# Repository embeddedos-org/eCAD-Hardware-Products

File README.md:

# eCAD Hardware Products

Hardware / PCB CAD design collection for the **EmbeddedOS (EoS)** ecosystem.
The repository organizes hardware product designs by application domain. Each
domain holds one or more product lines, and each product line typically carries
a product datasheet, a bill of materials (`bom.csv`), power-budget simulation
scripts, and placeholder directories for PCB and mechanical CAD artifacts.
Several product lines also include KiCad schematics (`*.kicad_sch`).

> Status varies by design. Directories are at different maturity levels (many
> "Design" / "Pre-production"); PCB and CAD folders often contain `.gitkeep`
> placeholders rather than finished layouts. Check each design's own `README.md`
> and `docs/` for its current state.

## Domains

The repository contains **16** domain design collections:

| Domain | Focus |
|---|---|
| `eAerospace_CAD_Design` | Aircraft components, avionics, UAV/drone systems, space systems |
| `eConsumer_CAD_Design` | Smart home devices, personal wearables, AR/smart devices |
| `eCybersecurity_CAD_Design` | Security appliances and physical security systems |
| `eDefense_CAD_Design` | Surveillance, tactical communications, protection equipment |
| `eElectronics_CAD_Design` | PCBs, embedded controllers, RF modules, FPGAs, AI accelerators |
| `eEnergy_CAD_Design` | Battery products, renewable energy systems, power electronics |
| `eHealth365_CAD_Design` | Two-device health monitoring system (smart patch / smart ring) |
| `eIndustrial_CAD_Design` | Sensors, industrial electronics, infrastructure equipment |
| `eMedical_CAD_Design` | Diagnostic, surgical, patient-care, laboratory equipment |
| `eMining_CAD_Design` | Autonomous mining/construction equipment, industrial safety systems |
| `ePAM_CAD_Design` | Personal air/ground mobility — solar-hybrid transport, 4-product line |
| `eRadar360_CAD_Design` | 360° automotive safety radar + laser + V2X + AI threat detection |
| `eRobotics_CAD_Design` | Industrial robots, autonomous systems, robot components |
| `eSmartCity_CAD_Design` | Urban infrastructure, utilities, telecommunications |
| `eTransport_CAD_Design` | Automotive electronics, rail systems, maritime systems |
| `eosHealth_CAD_Design` | Four-device wearable health platform |

Plus:

- `future_designs/` — early/prospective concepts (e.g. `eBCI-Lite`)
- `docs/` — repository-level documentation

## Typical design layout

Most domains follow a common structure, for example:

```
eAerospace_CAD_Design/
  README.md
  docs/                      business_plan.md, regulatory_path.md
  ebuild_simulation/         eBuild simulation notes
  <product_line>/
    product_datasheet.md
    bom.csv
    simulation/power_budget_sim.py
    hardware/
      pcb/  cad/  antenna/   (artifact folders; often .gitkeep placeholders)
```

Artifact formats present in the repo include Markdown datasheets, CSV BOMs,
Python simulation scripts, and KiCad schematics (`*.kicad_sch`). Some product
lines also include TypeScript/Dart companion app sources and 3D-model notes.

## Simulations

Power-budget simulations are plain Python scripts, runnable per product line:

```bash
cd eAerospace_CAD_Design/<product_line>/simulation/
python3 power_budget_sim.py
```

Design docs reference the [EoSim](https://github.com/embeddedos-org/EoSim)
digital-twin platform for hardware-in-the-loop testing. Running one script alone
does not establish that a product is validated.

## Evidence-backed product validation

The committed `tools/catalog/product_inventory.json` is the complete product
execution set. The v1 contract schemas and policy requirements are documented in
`docs/hardware-validation-contract-v1.md`.

Discover inventory drift and inspect local tool capabilities:

```bash
python3 tools/validate_products.py discover
python3 tools/validate_products.py capabilities
```

Execute V0-V4 for every inventoried product and write hash-bound receipts:

```bash
python3 tools/validate_products.py validate \
  --all \
  --output /tmp/ecad-validation \
  --mode evidence
python3 tools/validate_products.py verify-bundle \
  /tmp/ecad-validation/bundle.json
```

`--mode evidence` succeeds when the selected inventory was executed and valid
receipts were written. Individual products may still be honestly `FAIL`,
`BLOCKED`, `INCONCLUSIVE`, or `NOT_RUN`. Use `--mode gate` for a release check;
it succeeds only when every selected product has real `PASS` evidence for V0,
V1, V2, V3, and V4. Historical baseline entries never waive a failed or missing
requirement.

## License

MIT — see [LICENSE](LICENSE).

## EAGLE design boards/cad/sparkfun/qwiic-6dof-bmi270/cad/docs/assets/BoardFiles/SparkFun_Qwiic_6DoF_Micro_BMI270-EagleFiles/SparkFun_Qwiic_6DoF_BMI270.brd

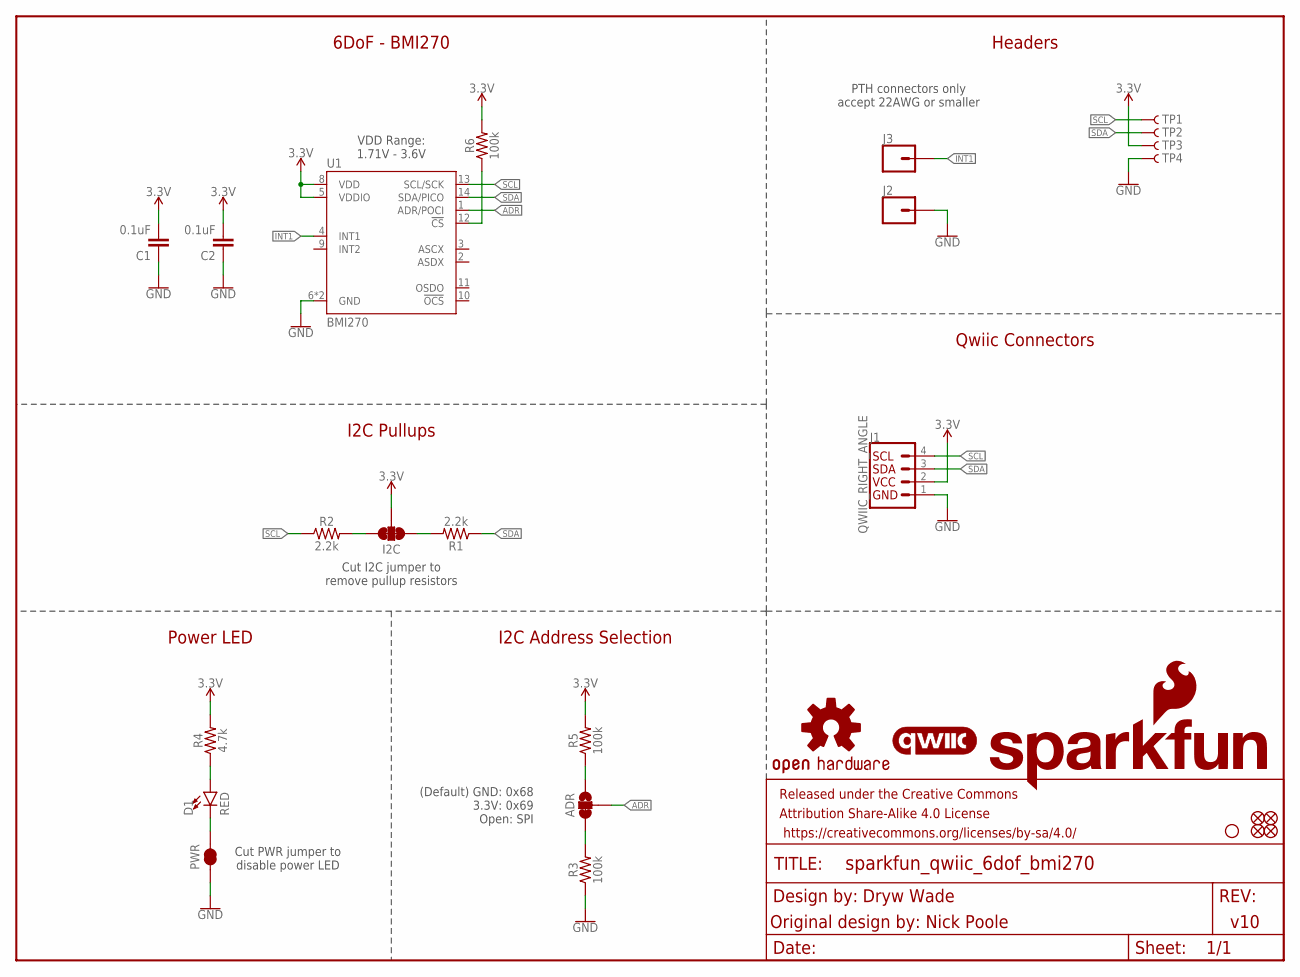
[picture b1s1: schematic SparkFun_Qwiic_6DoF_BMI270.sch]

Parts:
ADR: JUMPER-SMT_3_1-NC_TRACE_SILK; SMT-JUMPER_3_1-NC_TRACE_SILK
C1, C2: 0.1uF; 0402-TIGHT
D1: RED; LED-0402
FD1, FD2, FD3, FD4: FIDUCIALUFIDUCIAL; FIDUCIAL-MICRO
FRAME1: FRAME-LETTER; CREATIVE_COMMONS
H1: STAND-OFF
I2C: JUMPER-SMT_3_2-NC_TRACE_SILK; SMT-JUMPER_3_2-NC_TRACE_SILK
J1: QWIIC_RIGHT_ANGLE; JST04_1MM_RA
J2, J3: CONN_01_1MM; 1X01_1MM_NO_SILK
LOGO1: SFE_LOGO_NAME_FLAMEBLANK; BLANK
LOGO2: QWIIC_LOGO_3MM; QWIIC_3MM
LOGO3: OSHW-LOGOMINI; OSHW-LOGO-MINI
PWR: JUMPER-SMT_2_NC_TRACE_SILK; SMT-JUMPER_2_NC_TRACE_SILK
R1, R2: 2.2k; 0402-TIGHT
R3, R5, R6: 100k; 0402-TIGHT
R4: 4.7k; 0402-TIGHT
TP1, TP2, TP3, TP4: TEST-POINT3; PAD.03X.03
U1: BMI270

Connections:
3.3V: C1.2, C2.2, I2C.2, J1.2, R4.2, R5.2, R6.2, TP3.1, U1.5 (VDDIO), U1.8 (VDD)
ADR: ADR.2, U1.1 (ADR/POCI)
GND: C1.1, C2.1, J1.1, J2.1, PWR.1, R3.1, TP4.1, U1.6 (GND), U1.7 (GND)
INT1: J3.1, U1.4 (INT1)
unnamed: I2C.1, R1.2
unnamed: I2C.3, R2.2
unnamed: D1.C, PWR.2
unnamed: D1.A, R4.1
unnamed: ADR.1, R5.1
unnamed: ADR.3, R3.2
unnamed: R6.1, U1.12 (!CS!)
SCL: J1.4, R2.1, TP1.1, U1.13 (SCL/SCK)
SDA: J1.3, R1.1, TP2.1, U1.14 (SDA/PICO)

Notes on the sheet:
(Default) GND: 0x68 3.3V: 0x69 Open: SPI
Cut PWR jumper to disable power LED
Power LED
Headers
Qwiic Connectors
Dryw Wade
Original design by: Nick Poole
v10
6DoF - BMI270
Cut I2C jumper to remove pullup resistors
VDD Range: 1.71V - 3.6V
I2C Address Selection
I2C Pullups
PTH connectors only accept 22AWG or smaller

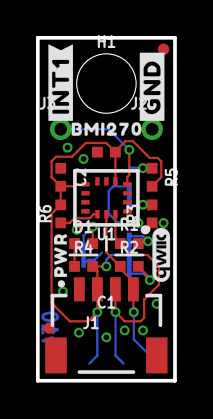
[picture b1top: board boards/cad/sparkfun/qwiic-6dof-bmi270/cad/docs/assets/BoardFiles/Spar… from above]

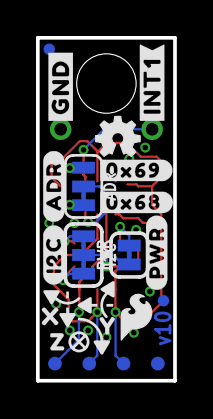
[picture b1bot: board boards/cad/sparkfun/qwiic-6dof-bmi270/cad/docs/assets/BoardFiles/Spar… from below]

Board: 2 copper layers, 7.6 x 19.1 mm, 45 parts (22 on the bottom side), 13 nets.

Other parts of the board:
U$1: #I2C#0
U$2, U$7: #GND#0
U$3: SFE_LOGO_FLAME_.1
U$4: #PWR#0
U$5: #ADR#0
U$6: #0X68#0
U$8, U$9: #INT1#0
U$18: #0X69#0
U$21: BMI2700
U$33: ORDERING_INSTRUCTIONS
U$34: PWR0
U$79: X0
U$80: Y0
U$81: Z0

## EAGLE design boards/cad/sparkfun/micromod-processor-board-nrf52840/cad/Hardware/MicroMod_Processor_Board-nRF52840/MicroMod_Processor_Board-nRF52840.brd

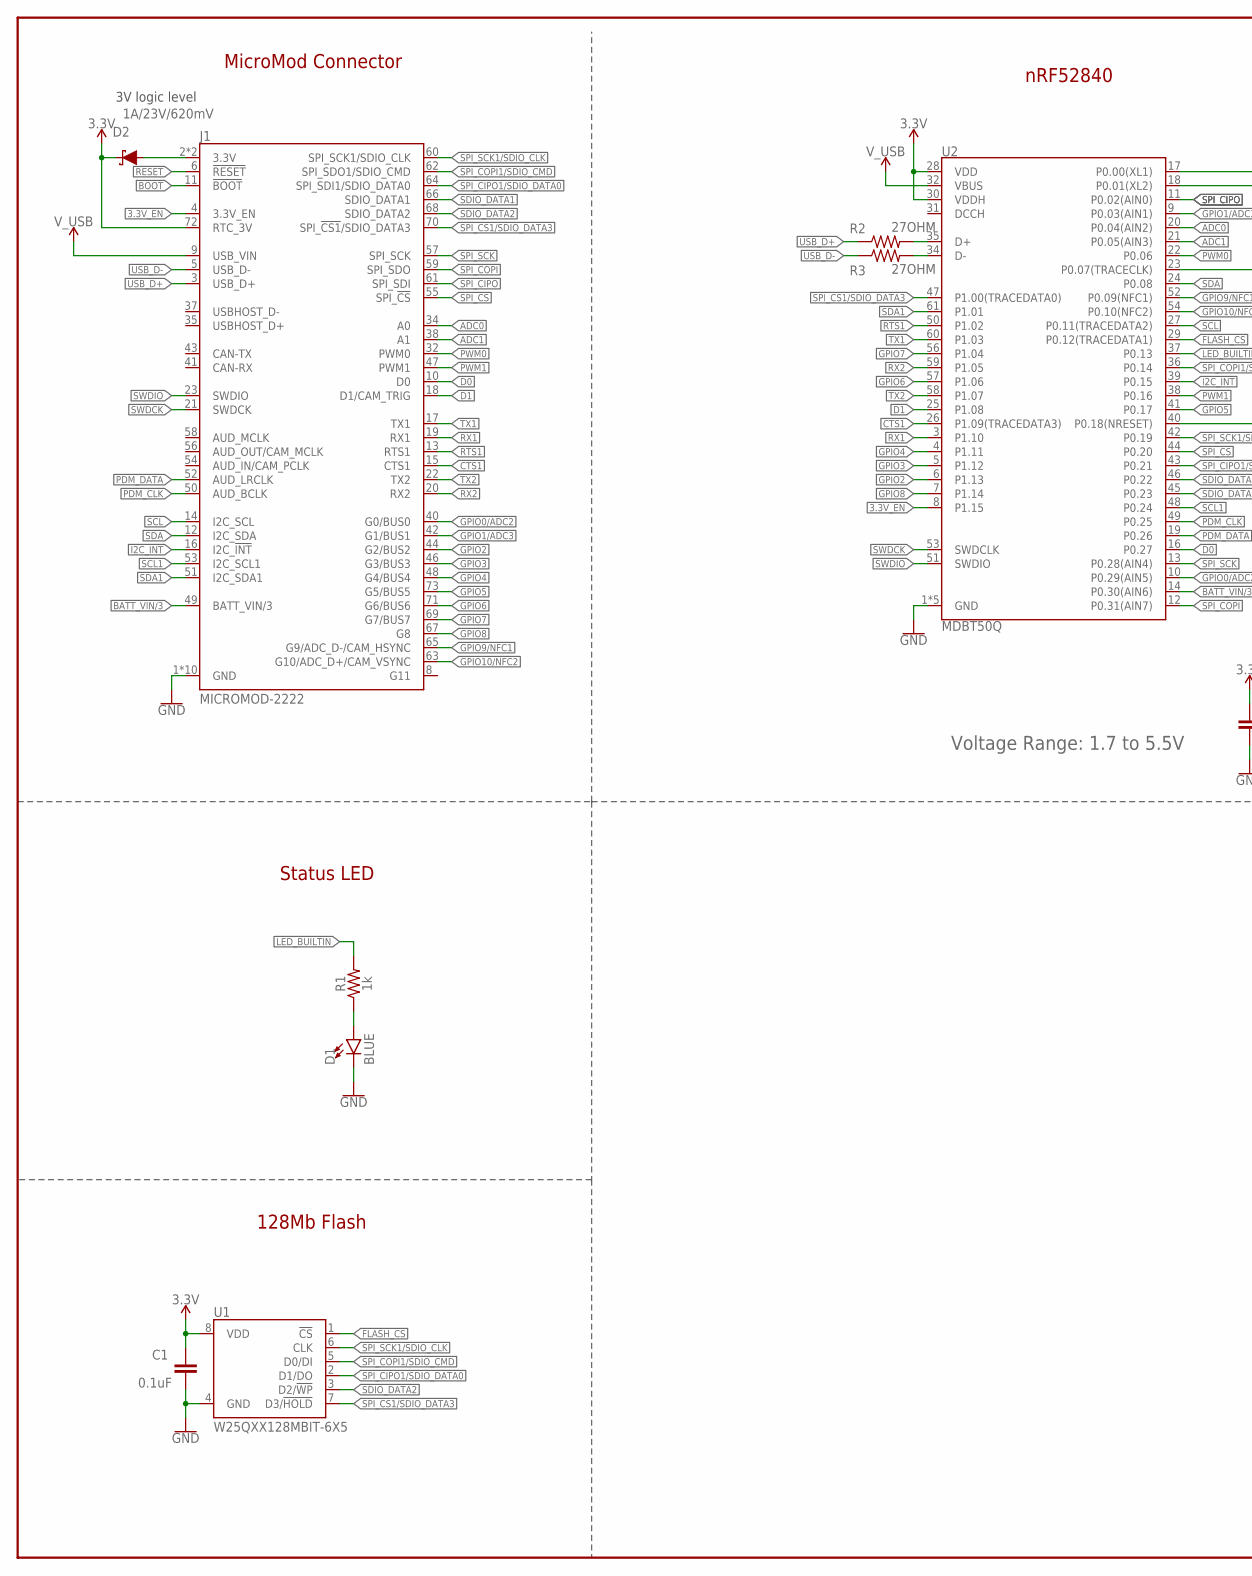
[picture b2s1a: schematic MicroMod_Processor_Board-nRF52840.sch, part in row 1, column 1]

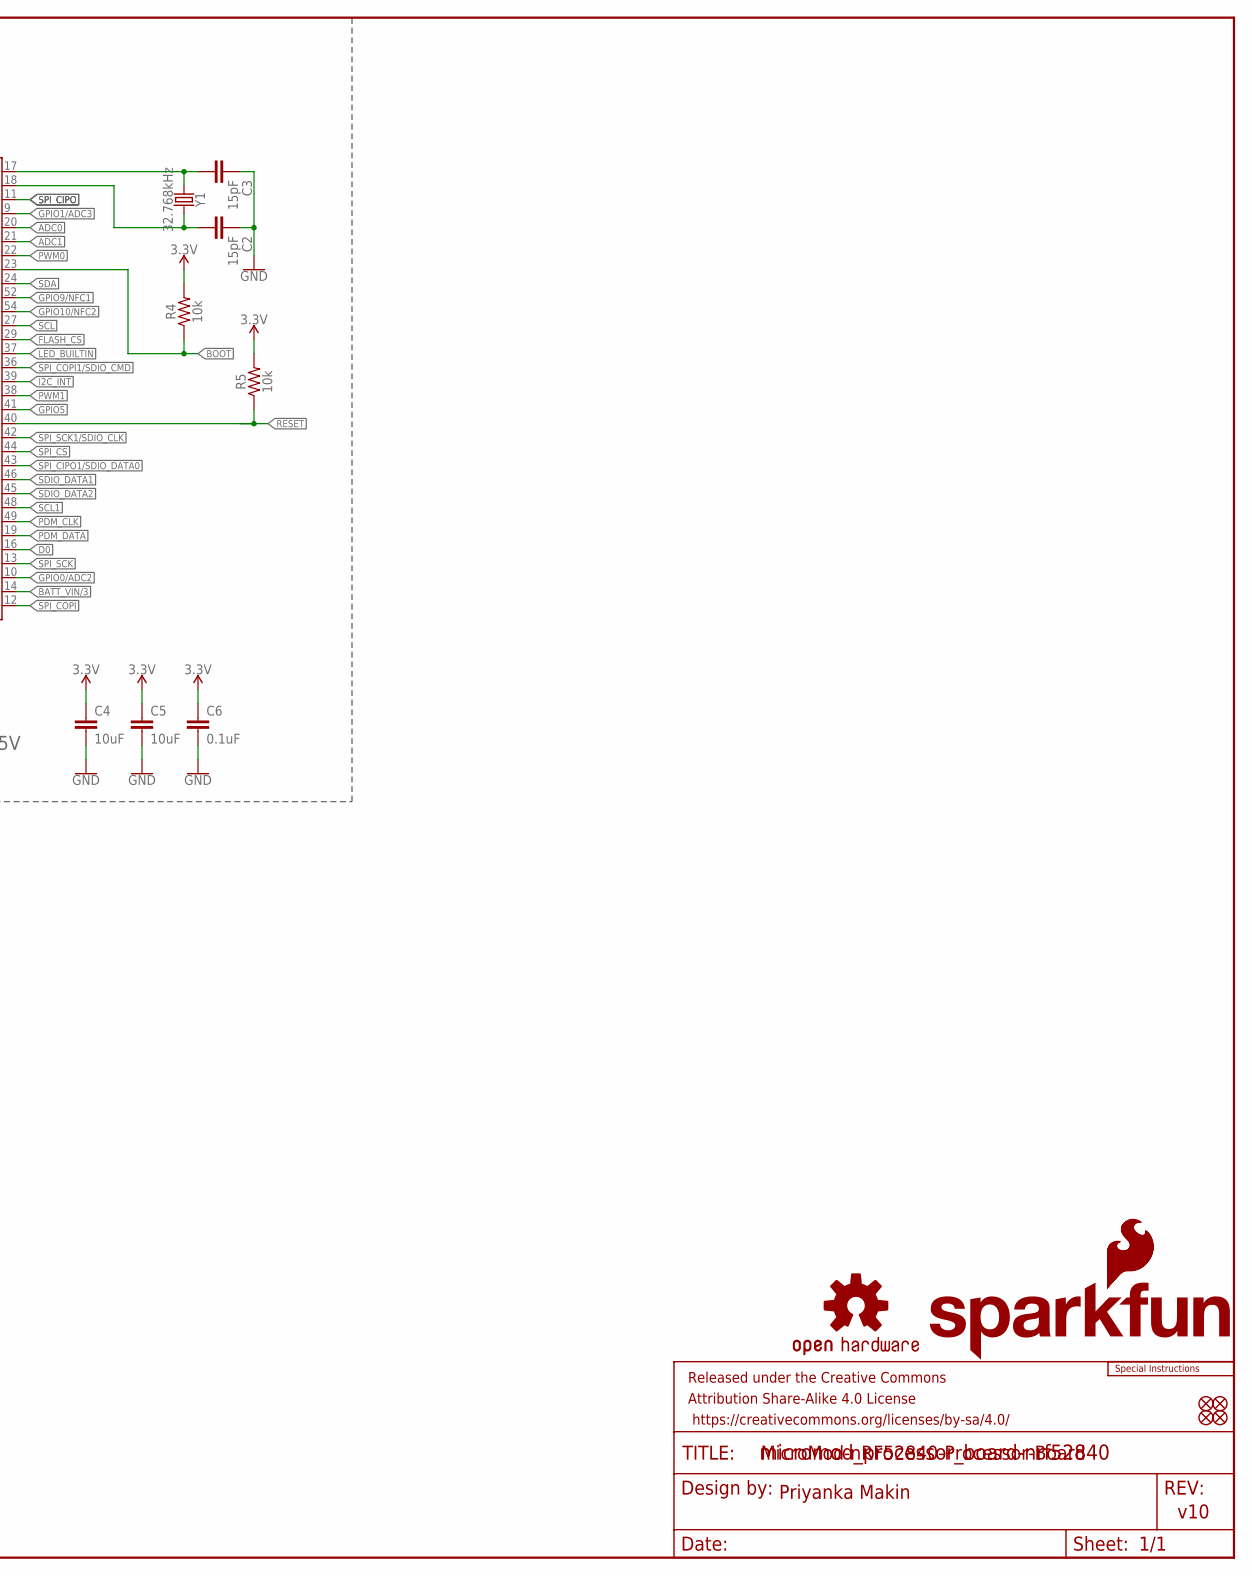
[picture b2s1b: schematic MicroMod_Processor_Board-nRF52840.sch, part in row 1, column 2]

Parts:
C1, C6: 0.1uF; 0402-TIGHT
C2, C3: 15pF; 0402-TIGHT
C4, C5: 10uF; 0402-TIGHT
D1: BLUE; LED-0603
D2: 1A/23V/620mV; SOD-323
FD1, FD2, FD3, FD4: FIDUCIALUFIDUCIAL; FIDUCIAL-MICRO
FRAME1: FRAME-LEDGER; CREATIVE_COMMONS
J1: MICROMOD-2222; M.2-CARD-E-22
LOGO1: SFE_LOGO_NAME_FLAME.1_INCH; SFE_LOGO_NAME_FLAME_.1
LOGO2: SFE_LOGO_FLAME.1_INCH; SFE_LOGO_FLAME_.1
LOGO3: OSHW-LOGOMINI; OSHW-LOGO-MINI
LOGO4: SPECIAL_INSTRUCTIONS-ORDERING; ORDERING_INSTRUCTIONS
R1: 1k; 0402-TIGHT
R2, R3: 27OHM; 0402-TIGHT
R4, R5: 10k; 0402-TIGHT
U1: W25QXX128MBIT-6X5; WSON-8-6X5
U2: MDBT50Q
Y1: 32.768kHz; CRYSTAL-SMD-3.2X1.5MM

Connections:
3.3V: C1.1, C4.1, C5.1, C6.1, D2.C, J1.72 (RTC_3V), R4.2, R5.2, U1.8 (VDD), U2.28 (VDD), U2.30 (VDDH)
3.3V_EN: J1.4 (3.3V_EN), U2.8 (P1.15)
!BOOT!: J1.11 (!BOOT!), R4.1, U2.23 (P0.07(TRACECLK))
!RESET!: J1.6 (!RESET!), R5.1, U2.40 (P0.18(NRESET))
ADC0: J1.34 (A0), U2.20 (P0.04(AIN2))
ADC1: J1.38 (A1), U2.21 (P0.05(AIN3))
BATT_VIN/3: J1.49 (BATT_VIN/3), U2.14 (P0.30(AIN6))
CTS1: J1.15 (CTS1), U2.26 (P1.09(TRACEDATA3))
D0: J1.10 (D0), U2.16 (P0.27)
D1: J1.18 (D1/CAM_TRIG), U2.25 (P1.08)
FLASH_!CS!: U1.1 (!CS!), U2.29 (P0.12(TRACEDATA1))
GND: C1.2, C2.1, C3.1, C4.2, C5.2, C6.2, D1.C, J1.1 (GND), J1.7 (GND), J1.33 (GND), J1.36 (GND), J1.39 (GND), J1.45 (GND), J1.75 (GND), J1.GND1 (GND), J1.GND2 (GND), J1.GND3 (GND), U1.4 (GND), U2.1 (GND), U2.2 (GND), U2.15 (GND), U2.33 (GND), U2.55 (GND)
GPIO0/ADC2: J1.40 (G0/BUS0), U2.10 (P0.29(AIN5))
GPIO1/ADC3: J1.42 (G1/BUS1), U2.9 (P0.03(AIN1))
GPIO2: J1.44 (G2/BUS2), U2.6 (P1.13)
GPIO3: J1.46 (G3/BUS3), U2.5 (P1.12)
GPIO4: J1.48 (G4/BUS4), U2.4 (P1.11)
GPIO5: J1.73 (G5/BUS5), U2.41 (P0.17)
GPIO6: J1.71 (G6/BUS6), U2.57 (P1.06)
GPIO7: J1.69 (G7/BUS7), U2.56 (P1.04)
GPIO8: J1.67 (G8), U2.7 (P1.14)
GPIO9/NFC1: J1.65 (G9/ADC_D-/CAM_HSYNC), U2.52 (P0.09(NFC1))
GPIO10/NFC2: J1.63 (G10/ADC_D+/CAM_VSYNC), U2.54 (P0.10(NFC2))
I2C_!INT!: J1.16 (I2C_!INT!), U2.39 (P0.15)
LED_BUILTIN: R1.2, U2.37 (P0.13)
unnamed: R2.2, U2.35 (D+)
unnamed: D1.A, R1.1
unnamed: R3.2, U2.34 (D-)
unnamed: C3.2, U2.17 (P0.00(XL1)), Y1.P$1 (1)
unnamed: D2.A, J1.2 (3.3V), J1.74 (3.3V)
unnamed: C2.2, U2.18 (P0.01(XL2)), Y1.P$2 (2)
PDM_CLK: J1.50 (AUD_BCLK), U2.49 (P0.25)
PDM_DATA: J1.52 (AUD_LRCLK), U2.19 (P0.26)
PWM0: J1.32 (PWM0), U2.22 (P0.06)
PWM1: J1.47 (PWM1), U2.38 (P0.16)
RTS1: J1.13 (RTS1), U2.50 (P1.02)
RX1: J1.19 (RX1), U2.3 (P1.10)
RX2: J1.20 (RX2), U2.59 (P1.05)
SCL: J1.14 (I2C_SCL), U2.27 (P0.11(TRACEDATA2))
SCL1: J1.53 (I2C_SCL1), U2.48 (P0.24)
SDA: J1.12 (I2C_SDA), U2.24 (P0.08)
SDA1: J1.51 (I2C_SDA1), U2.61 (P1.01)
SDIO_DATA1: J1.66 (SDIO_DATA1), U2.46 (P0.22)
SDIO_DATA2: J1.68 (SDIO_DATA2), U1.3 (D2/!WP!), U2.45 (P0.23)
SPI_!CS1!/SDIO_DATA3: J1.70 (SPI_!CS1!/SDIO_DATA3), U1.7 (D3/!HOLD!), U2.47 (P1.00(TRACEDATA0))
SPI_!CS!: J1.55 (SPI_!CS!), U2.44 (P0.20)
SPI_CIPO: J1.61 (SPI_SDI), U2.11 (P0.02(AIN0))
SPI_CIPO1/SDIO_DATA0: J1.64 (SPI_SDI1/SDIO_DATA0), U1.2 (D1/DO), U2.43 (P0.21)
SPI_COPI: J1.59 (SPI_SDO), U2.12 (P0.31(AIN7))
SPI_COPI1/SDIO_CMD: J1.62 (SPI_SDO1/SDIO_CMD), U1.5 (D0/DI), U2.36 (P0.14)
SPI_SCK: J1.57 (SPI_SCK), U2.13 (P0.28(AIN4))
SPI_SCK1/SDIO_CLK: J1.60 (SPI_SCK1/SDIO_CLK), U1.6 (CLK), U2.42 (P0.19)
SWDCK: J1.21 (SWDCK), U2.53 (SWDCLK)
SWDIO: J1.23 (SWDIO), U2.51 (SWDIO)
TX1: J1.17 (TX1), U2.60 (P1.03)
TX2: J1.22 (TX2), U2.58 (P1.07)
USB_D+: J1.3 (USB_D+), R2.1
USB_D-: J1.5 (USB_D-), R3.1
V_USB: J1.9 (USB_VIN), U2.32 (VBUS)

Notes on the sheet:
MicroMod Connector
Status LED
MicroMod-nRF52840-Processor-Board
Priyanka Makin
v10
128Mb Flash
Voltage Range: 1.7 to 5.5V
nRF52840
3V logic level

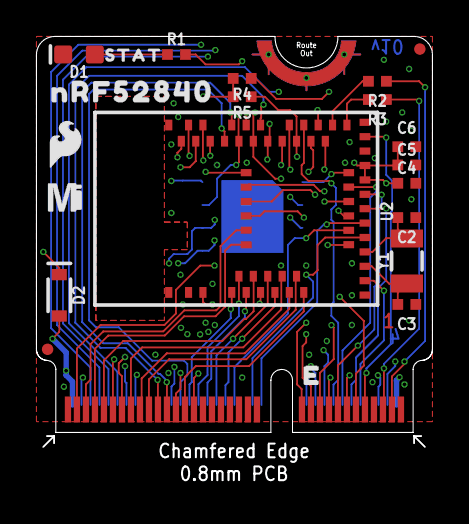
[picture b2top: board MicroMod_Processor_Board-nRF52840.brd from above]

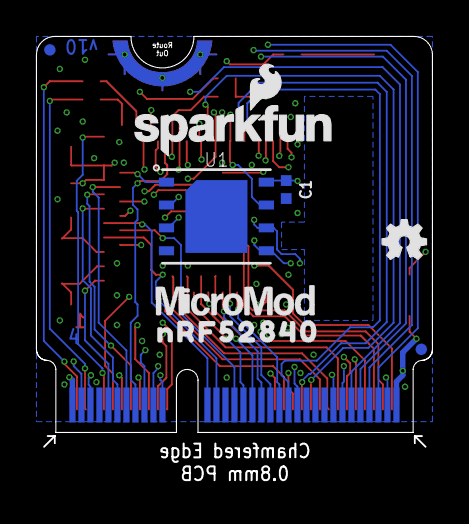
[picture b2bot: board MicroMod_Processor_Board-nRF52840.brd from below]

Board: 4 copper layers, 22.0 x 22.8 mm, 31 parts (8 on the bottom side), 59 nets.

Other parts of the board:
U$1: MICROMOD_MI_LOGO_.35
U$2: STAT0
U$3, U$6: NRF528400
U$5: MICROMOD_LOGO_.35

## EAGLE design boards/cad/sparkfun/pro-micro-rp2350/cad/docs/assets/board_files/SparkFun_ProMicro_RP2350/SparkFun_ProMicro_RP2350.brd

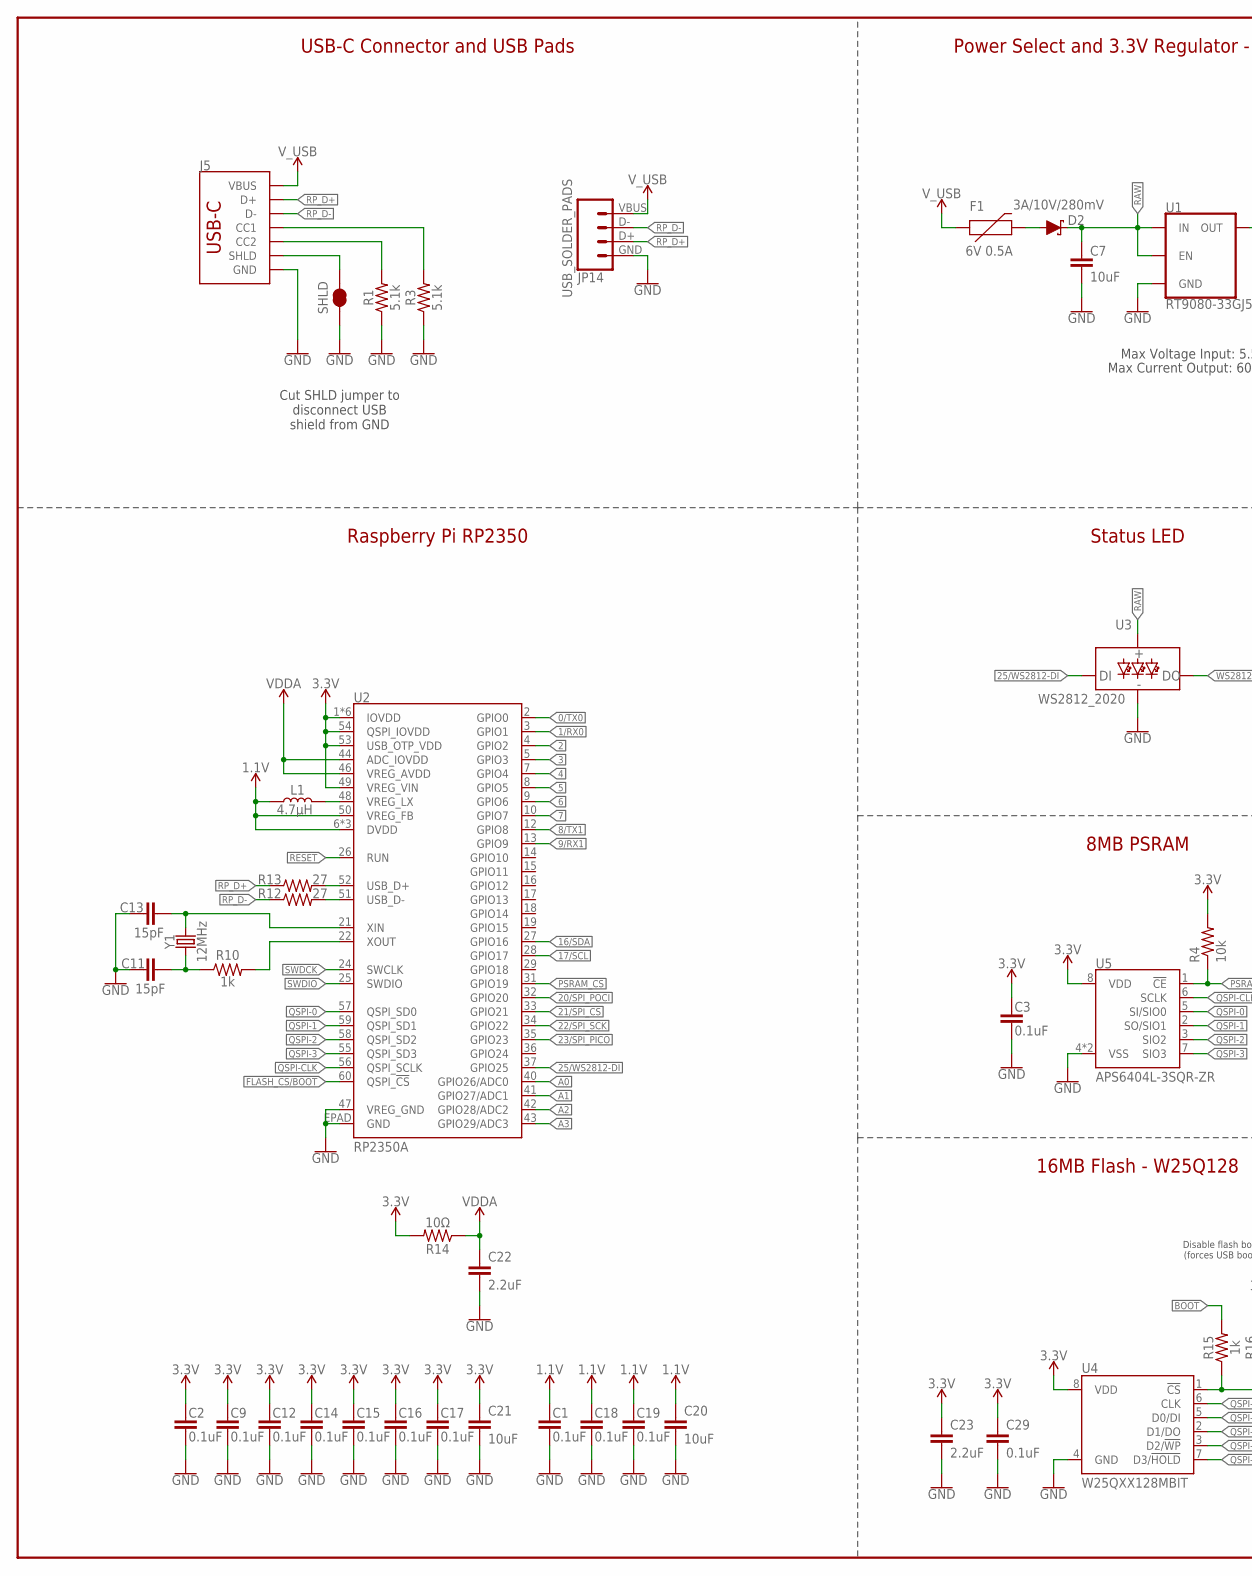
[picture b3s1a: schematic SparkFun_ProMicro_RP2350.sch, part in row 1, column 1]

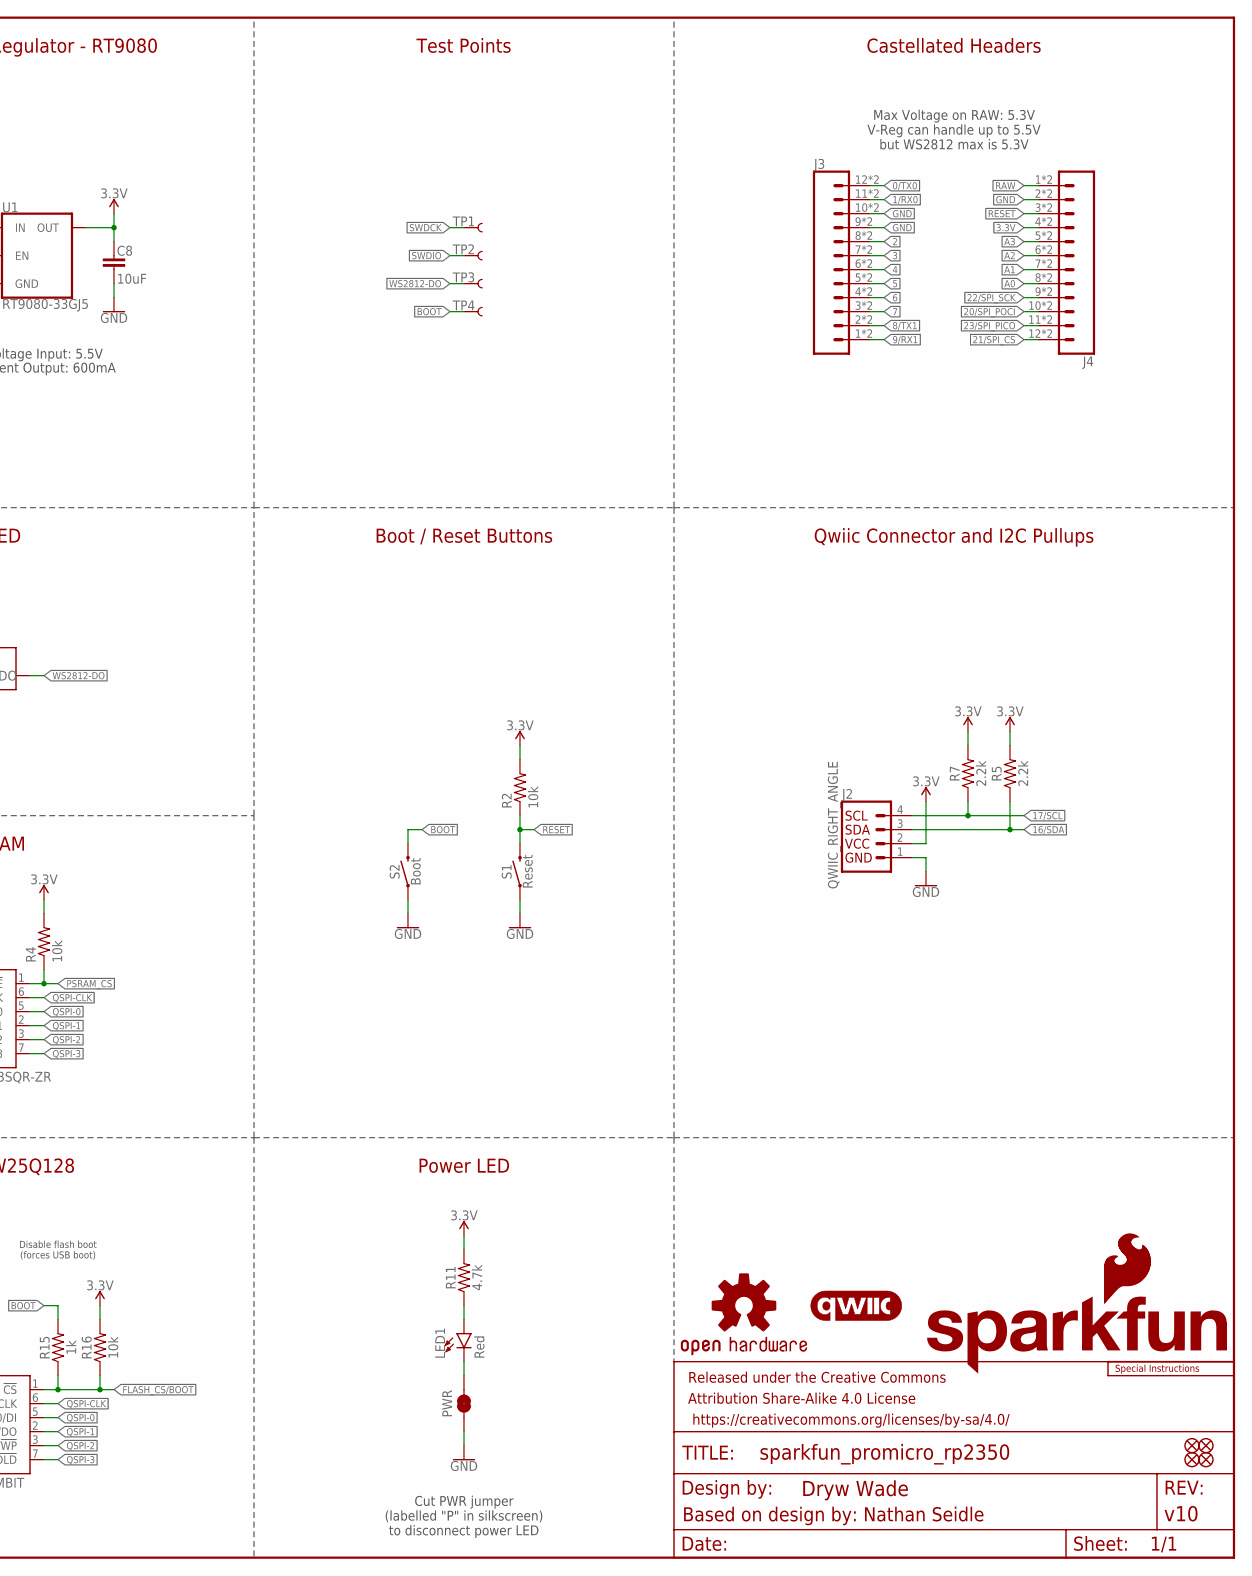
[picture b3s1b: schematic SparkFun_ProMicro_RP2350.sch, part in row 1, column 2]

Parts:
C1, C2, C3, C9, C12, C14, C15, C16, C17, C18, C19, C29: 0.1uF; 0402-TIGHT
C7, C8, C20, C21: 10uF; 0402-TIGHT
C11, C13: 15pF; 0402-TIGHT
C22, C23: 2.2uF; 0402-TIGHT
D2: 3A/10V/280mV; SOD-323
F1: 6V 0.5A; 0805
FRAME2: FRAME-LEDGER; CREATIVE_COMMONS
J2: QWIIC_RIGHT_ANGLE; JST04_1MM_RA
J3, J4: CONN_12CASTELLATED; 1X12_CASTELLATED
J5: USB Female Type C Connector; USB-C-16P_4LAYER-PADS
JP1, JP2, JP3, JP4: FIDUCIAL1X2; FIDUCIAL-1X2
JP14: USB_SOLDER_PADS; USB-SOLDER-PADS
L1: 4.7μH; 1008(2520)
LED1: Red; LED-0603
LOGO1: SFE_LOGO_NAME_FLAME.1_INCH; SFE_LOGO_NAME_FLAME_.1
LOGO3: QWIIC_LOGO_6MM; QWIIC_6MM
LOGO4: SFE_LOGO_FLAME.1_INCH; SFE_LOGO_FLAME_.1
LOGO5: SPECIAL_INSTRUCTIONS-ORDERING; ORDERING_INSTRUCTIONS
PWR: JUMPER-SMT_2_NC_TRACE_SILK; SMT-JUMPER_2_NC_TRACE_SILK
R1, R3: 5.1k; 0402-TIGHT
R2, R4, R16: 10k; 0402-TIGHT
R5, R7: 2.2k; 0402-TIGHT
R10, R15: 1k; 0402-TIGHT
R11: 4.7k; 0402-TIGHT
R12, R13: 27; 0402-TIGHT
R14: 10Ω; 0402-TIGHT
S1: Reset; TACTILE_SWITCH_SMD_4.6X2.8MM
S2: Boot; TACTILE_SWITCH_SMD_4.6X2.8MM
SHLD: JUMPER-SMT_2_NC_TRACE_SILK; SMT-JUMPER_2_NC_TRACE_SILK
TP1, TP2, TP3, TP4: TEST-POINT3X5; PAD.03X.05
U1: RT9080-33GJ5; SOT23-5
U2: RP2350A
U3: WS2812_2020; WS2812-2020
U4: W25QXX128MBIT; WSON-8-6X5-SKINNY_CENTERPAD
U5: APS6404L-3SQR-ZR
U$3: OSHW-LOGOMINI; OSHW-LOGO-MINI
Y1: 12MHz; CRYSTAL-SMD-2X2.5MM

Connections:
0/TX0: J3.12, J3.12B (12), U2.2 (GPIO0)
1.1V: C1.1, C18.1, C19.1, C20.1, L1.1, U2.6 (DVDD), U2.23 (DVDD), U2.39 (DVDD), U2.50 (VREG_FB)
1/RX0: J3.11, J3.11B (11), U2.3 (GPIO1)
2: J3.8, J3.8B (8), U2.4 (GPIO2)
3: J3.7, J3.7B (7), U2.5 (GPIO3)
3.3V: C2.1, C3.1, C8.2, C9.1, C12.1, C14.1, C15.1, C16.1, C17.1, C21.1, C23.1, C29.1, J2.2, J4.4, J4.4B (4), R2.2, R4.2, R5.2, R7.2, R11.2, R14.2, R16.2, U1.5 (OUT), U2.1 (IOVDD), U2.11 (IOVDD), U2.20 (IOVDD), U2.30 (IOVDD), U2.38 (IOVDD), U2.45 (IOVDD), U2.49 (VREG_VIN), U2.53 (USB_OTP_VDD), U2.54 (QSPI_IOVDD), U4.8 (VDD), U5.8 (VDD)
4: J3.6, J3.6B (6), U2.7 (GPIO4)
5: J3.5, J3.5B (5), U2.8 (GPIO5)
6: J3.4, J3.4B (4), U2.9 (GPIO6)
7: J3.3, J3.3B (3), U2.10 (GPIO7)
8/TX1: J3.2, J3.2B (2), U2.12 (GPIO8)
9/RX1: J3.1, J3.1B (1), U2.13 (GPIO9)
16/SDA: J2.3, R5.1, U2.27 (GPIO16)
17/SCL: J2.4, R7.1, U2.28 (GPIO17)
20/SPI_POCI: J4.10, J4.10B (10), U2.32 (GPIO20)
21/SPI_!CS!: J4.12, J4.12B (12), U2.33 (GPIO21)
22/SPI_SCK: J4.9, J4.9B (9), U2.34 (GPIO22)
23/SPI_PICO: J4.11, J4.11B (11), U2.35 (GPIO23)
25/WS2812-DI: U2.37 (GPIO25), U3.DI
!RESET!: J4.3, J4.3B (3), R2.1, S1.3 (2), S1.4 (2), U2.26 (RUN)
A0: J4.8, J4.8B (8), U2.40 (GPIO26/ADC0)
A1: J4.7, J4.7B (7), U2.41 (GPIO27/ADC1)
A2: J4.6, J4.6B (6), U2.42 (GPIO28/ADC2)
A3: J4.5, J4.5B (5), U2.43 (GPIO29/ADC3)
BOOT: R15.2, S2.3 (2), S2.4 (2), TP4.1
FLASH_!CS!/BOOT: R15.1, R16.1, U2.60 (QSPI_!CS!), U4.1 (!CS!)
GND: C1.2, C2.2, C3.2, C7.1, C8.1, C9.2, C11.1, C12.2, C13.1, C14.2, C15.2, C16.2, C17.2, C18.2, C19.2, C20.2, C21.2, C22.2, C23.2, C29.2, J2.1, J3.9, J3.9B (9), J3.10, J3.10B (10), J4.2, J4.2B (2), J5.GND, J5.GND2 (GND), JP14.GND (4), PWR.1, R1.1, R3.1, S1.1, S1.2 (1), S2.1, S2.2 (1), SHLD.2, U1.2 (GND), U2.47 (VREG_GND), U2.EPAD (GND), U3.GND, U4.4 (GND), U5.4 (VSS), U5.9 (VSS)
unnamed: L1.2, U2.48 (VREG_LX)
unnamed: LED1.C, PWR.2
unnamed: J5.A5 (CC1), R3.2
unnamed: J5.B5 (CC2), R1.2
unnamed: LED1.A, R11.1
PSRAM_!CS!: R4.1, U2.31 (GPIO19), U5.1 (!CE!)
QSPI-0: U2.57 (QSPI_SD0), U4.5 (D0/DI), U5.5 (SI/SIO0)
QSPI-1: U2.59 (QSPI_SD1), U4.2 (D1/DO), U5.2 (SO/SIO1)
QSPI-2: U2.58 (QSPI_SD2), U4.3 (D2/!WP!), U5.3 (SIO2)
QSPI-3: U2.55 (QSPI_SD3), U4.7 (D3/!HOLD!), U5.7 (SIO3)
QSPI-CLK: U2.56 (QSPI_SCLK), U4.6 (CLK), U5.6 (SCLK)
RAW: C7.2, D2.C, J4.1, J4.1B (1), U1.1 (IN), U1.3 (EN), U3.VCC
RP_D1+: R13.2, U2.52 (USB_D+)
RP_D1-: R12.2, U2.51 (USB_D-)
RP_D+: J5.A6 (D+), J5.B6 (D+), JP14.D+ (3), R13.1
RP_D-: J5.A7 (D-), J5.B7 (D-), JP14.D- (2), R12.1
SHLD: J5.SHLD1 (SHLD), J5.SHLD2 (SHLD), J5.SHLD3 (SHLD), J5.SHLD4 (SHLD), SHLD.1
SWDCK: TP1.1, U2.24 (SWCLK)
SWDIO: TP2.1, U2.25 (SWDIO)
USB_RAW: D2.A, F1.2
VDDA: C22.1, R14.1, U2.44 (ADC_IOVDD), U2.46 (VREG_AVDD)
V_USB: F1.1, J5.VBUS1 (VBUS), J5.VBUS2 (VBUS), JP14.VBUS (1)
WS2812-DO: TP3.1, U3.DO
X1A: R10.2, U2.22 (XOUT)
X1B: C11.2, R10.1, Y1.P1 (1)
X2: C13.2, U2.21 (XIN), Y1.P3 (2)

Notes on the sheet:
Max Voltage Input: 5.5V
Max Current Output: 600mA
Raspberry Pi RP2350
16MB Flash - W25Q128
Disable flash boot (forces USB boot)
Status LED
Power Select and 3.3V Regulator - RT9080
USB-C Connector and USB Pads
Castellated Headers
Boot / Reset Buttons
Max Voltage on RAW: 5.3V V-Reg can handle up to 5.5V but WS2812 max is 5.3V
Based on design by: Nathan Seidle
Cut SHLD jumper to disconnect USB shield from GND
Cut PWR jumper (labelled "P" in silkscreen) to disconnect power LED
Power LED
Qwiic Connector and I2C Pullups
Test Points
8MB PSRAM

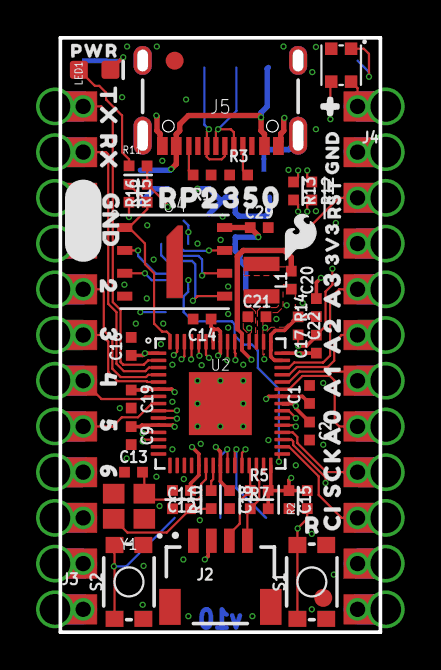
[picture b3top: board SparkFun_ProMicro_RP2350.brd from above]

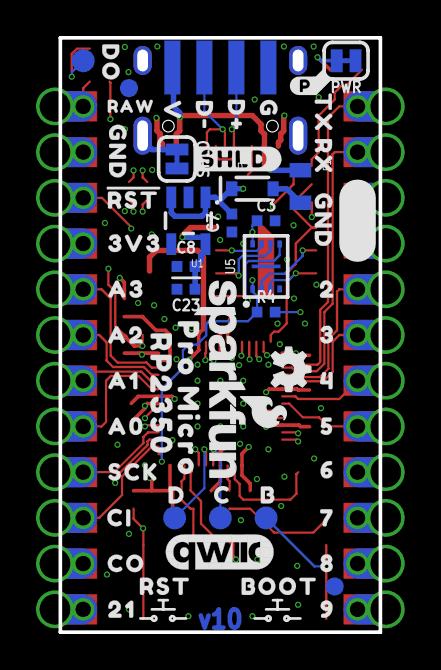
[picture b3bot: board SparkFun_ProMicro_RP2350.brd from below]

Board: 4 copper layers, 17.8 x 33.0 mm, 124 parts (58 on the bottom side), 53 nets.

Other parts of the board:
U$1, U$11: A00
U$2: GND_0
U$4: PRO_MICRO0
U$5: #0
U$6: 70
U$7: 81
U$8: 92
U$9, U$64: CI4
U$10, U$67: SCK3
U$12, U$20: A10
U$13, U$33: A21
U$14, U$39: A32
U$15, U$22, U$74: GND2
U$16: 3V3_0
U$17: RAW0
U$18: C0
U$19, U$76: TX0
U$21, U$75: RX1
U$23, U$53: 20
U$24, U$54: 31
U$25, U$55: 42
U$26, U$56: 53
U$27, U$57: 64
U$28: D#1
U$29: D#2
U$30: G0
U$31: V3
U$32: 210
U$34: #RST#0
U$35: D1
U$36: #P#0
U$37: R0
U$38: B0
U$40: DO0
U$41: BOOT0
U$42, U$45: RP23500
U$43: #SHLD#0
U$44: RST0
U$66: CO5
U$68: #RST#1
U$69: 3V30
U$73: PWR0

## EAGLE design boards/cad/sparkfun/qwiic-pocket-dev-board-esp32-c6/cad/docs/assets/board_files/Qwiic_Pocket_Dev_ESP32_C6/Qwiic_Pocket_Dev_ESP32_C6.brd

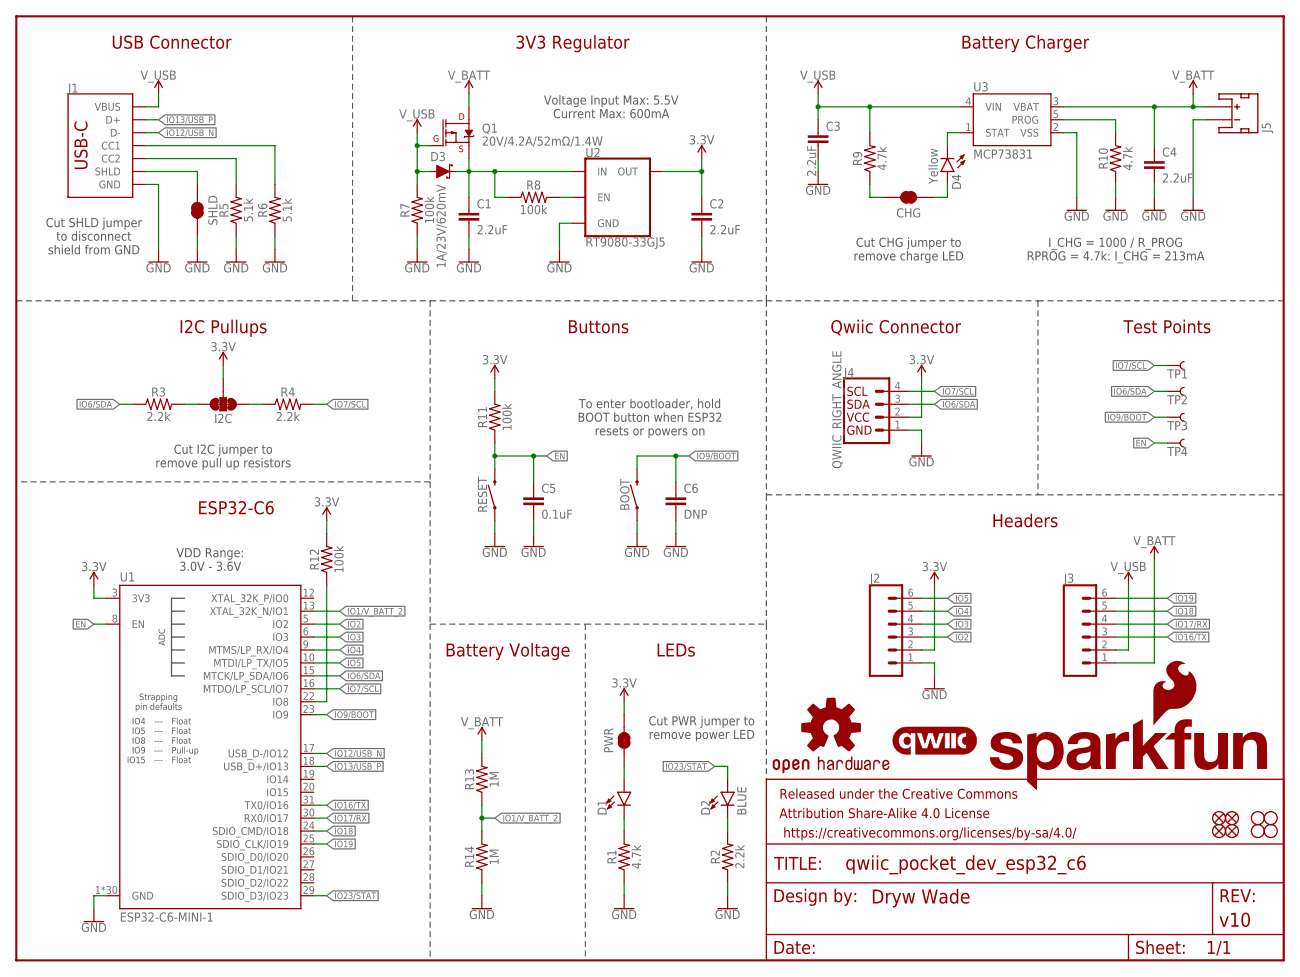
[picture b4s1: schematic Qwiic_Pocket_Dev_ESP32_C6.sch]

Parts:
BOOT: MOMENTARY-SWITCH-SPST-SMD-4.6X2.8MM; TACTILE_SWITCH_SMD_4.6X2.8MM
C1, C2, C3, C4: 2.2uF; 0402-TIGHT
C5: 0.1uF; 0402-TIGHT
C6: DNP; 0402-TIGHT
CHG: JUMPER-SMT_2_NC_TRACE_SILK; SMT-JUMPER_2_NC_TRACE_SILK
D1: LED-RED_0603-KB; LED-0603
D2: BLUE; LED-0603
D3: 1A/23V/620mV; SOD-323
D4: Yellow; LED-0603
FD1, FD2, FD3, FD4: FIDUCIALUFIDUCIAL; FIDUCIAL-MICRO
FRAME1: FRAME-LETTER; CREATIVE_COMMONS
H1, H2, H3, H4: STAND-OFF
I2C: JUMPER-SMT_3_2-NC_TRACE_SILK; SMT-JUMPER_3_2-NC_TRACE_SILK
J1: USB Female Type C Connector; USB-C-16P_4LAYER-PADS
J2, J3: CONN_06NO_SILK_NO_POP; 1X06_NO_SILK
J4: QWIIC_RIGHT_ANGLE; JST04_1MM_RA
J5: JST_2MM_MALE; JST-2-SMD
LOGO1: SFE_LOGO_NAME_FLAMEBLANK; BLANK
LOGO2: OSHW-LOGOS; OSHW-LOGO-S
LOGO3: QWIIC_LOGO_3MM; QWIIC_3MM
PWR: JUMPER-SMT_2_NC_TRACE_SILK; SMT-JUMPER_2_NC_TRACE_SILK
Q1: 20V/4.2A/52mΩ/1.4W; SOT23-3
R1, R9, R10: 4.7k; 0402-TIGHT
R2, R3, R4: 2.2k; 0402-TIGHT
R5, R6: 5.1k; 0402-TIGHT
R7, R8, R11, R12: 100k; 0402-TIGHT
R13, R14: 1M; 0402-TIGHT
RESET: MOMENTARY-SWITCH-SPST-SMD-4.6X2.8MM; TACTILE_SWITCH_SMD_4.6X2.8MM
SHLD: JUMPER-SMT_2_NC_TRACE_SILK; SMT-JUMPER_2_NC_TRACE_SILK
TP1, TP2, TP3, TP4: TEST-POINT3; PAD.03X.03
U1: ESP32-C6-MINI-1
U2: RT9080-33GJ5; SOT23-5
U3: MCP73831; SOT23-5

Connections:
3.3V: C2.1, I2C.2, J2.2, J4.2, PWR.2, R11.2, R12.2, U1.3 (3V3), U2.5 (OUT)
EN: C5.1, R11.1, RESET.3 (2), RESET.4 (2), TP4.1, U1.8 (EN)
GND: BOOT.1, BOOT.2 (1), C1.2, C2.2, C3.2, C4.2, C5.2, C6.2, J1.GND, J1.GND2 (GND), J2.1, J4.1, J5.1 (-), R1.1, R2.1, R5.1, R6.1, R7.1, R10.1, R14.1, RESET.1, RESET.2 (1), SHLD.2, U1.1 (GND), U1.2 (GND), U1.11 (GND), U1.14 (GND), U1.36 (GND), U1.37 (GND), U1.38 (GND), U1.39 (GND), U1.40 (GND), U1.41 (GND), U1.42 (GND), U1.43 (GND), U1.44 (GND), U1.45 (GND), U1.46 (GND), U1.47 (GND), U1.48 (GND), U1.49.1 (GND), U1.49.2 (GND), U1.49.3 (GND), U1.49.4 (GND), U1.49.5 (GND), U1.49.6 (GND), U1.49.7 (GND), U1.49.8 (GND), U1.49.9 (GND), U1.50 (GND), U1.51 (GND), U1.52 (GND), U1.53 (GND), U2.2 (GND), U3.2 (VSS)
IO1/V_BATT_2: R13.1, R14.2, U1.13 (XTAL_32K_N/IO1)
IO2: J2.3, U1.5 (IO2)
IO3: J2.4, U1.6 (IO3)
IO4: J2.5, U1.9 (MTMS/LP_RX/IO4)
IO5: J2.6, U1.10 (MTDI/LP_TX/IO5)
IO6/SDA: J4.3, R3.1, TP2.1, U1.15 (MTCK/LP_SDA/IO6)
IO7/SCL: J4.4, R4.2, TP1.1, U1.16 (MTDO/LP_SCL/IO7)
IO9/BOOT: BOOT.3 (2), BOOT.4 (2), C6.1, TP3.1, U1.23 (IO9)
IO12/USB_N: J1.A7 (D-), J1.B7 (D-), U1.17 (USB_D-/IO12)
IO13/USB_P: J1.A6 (D+), J1.B6 (D+), U1.18 (USB_D+/IO13)
IO16/TX: J3.3, U1.31 (TX0/IO16)
IO17/RX: J3.4, U1.30 (RX0/IO17)
IO18: J3.5, U1.24 (SDIO_CMD/IO18)
IO19: J3.6, U1.25 (SDIO_CLK/IO19)
IO23/STAT: D2.A, U1.29 (SDIO_D3/IO23)
unnamed: D1.C, R1.2
unnamed: D1.A, PWR.1
unnamed: D2.C, R2.2
unnamed: I2C.3, R3.2
unnamed: I2C.1, R4.1
unnamed: R8.2, U2.3 (EN)
unnamed: J1.B5 (CC2), R5.2
unnamed: J1.A5 (CC1), R6.2
unnamed: C1.1, D3.C, Q1.2 (S), R8.1, U2.1 (IN)
unnamed: D4.C, U3.1 (STAT)
unnamed: CHG.1, D4.A
unnamed: CHG.2, R9.1
unnamed: R10.2, U3.5 (PROG)
unnamed: R12.1, U1.22 (IO8)
SHLD: J1.SHLD1 (SHLD), J1.SHLD2 (SHLD), J1.SHLD3 (SHLD), J1.SHLD4 (SHLD), SHLD.1
V_BATT: C4.1, J3.1, J5.2 (+), Q1.3 (D), R13.2, U3.3 (VBAT)
V_USB: C3.1, D3.A, J1.VBUS1 (VBUS), J1.VBUS2 (VBUS), J3.2, Q1.1 (G), R7.2, R9.2, U3.4 (VIN)

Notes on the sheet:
USB Connector
3V3 Regulator
Battery Charger
Qwiic Connector
Headers
LEDs
Buttons
I2C Pullups
ESP32-C6
VDD Range: 3.0V - 3.6V
Cut I2C jumper to remove pull up resistors
Cut PWR jumper to remove power LED
Cut CHG jumper to remove charge LED
I_CHG = 1000 / R_PROG RPROG = 4.7k: I_CHG = 213mA
Test Points
Voltage Input Max: 5.5V Current Max: 600mA
To enter bootloader, hold BOOT button when ESP32 resets or powers on
Cut SHLD jumper to disconnect shield from GND
Battery Voltage

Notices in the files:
tools/eos_boards/boards/eos_kl25_board.py:
Copyright (c) 2026 Kartikeydheer Srivastava. All rights reserved: this design file is not under
the repository's MIT licence; see boards/eos/eos-kl25-board/LICENSE.txt.
parts and their libraries:
SparkFun-Aesthetics: Licensing: Creative Commons ShareAlike 4.0 International - https://creativecommons.org/licenses/by-sa/4.0
SparkFun-Aesthetics: Released under the Creative Commons Attribution Share-Alike 4.0 License
SparkFun-Aesthetics: https://creativecommons.org/licenses/by-sa/4.0
